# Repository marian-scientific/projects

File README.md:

# projects
project data, records &amp; publications

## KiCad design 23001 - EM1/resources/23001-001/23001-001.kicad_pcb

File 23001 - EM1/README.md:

# 23001 - EM1
### *Educational Manipulative 1*: Inequalities

## Associated Part Numbers:
- [23001-001](resources/23001-001/): USB-C charging LiPo power distribution test board

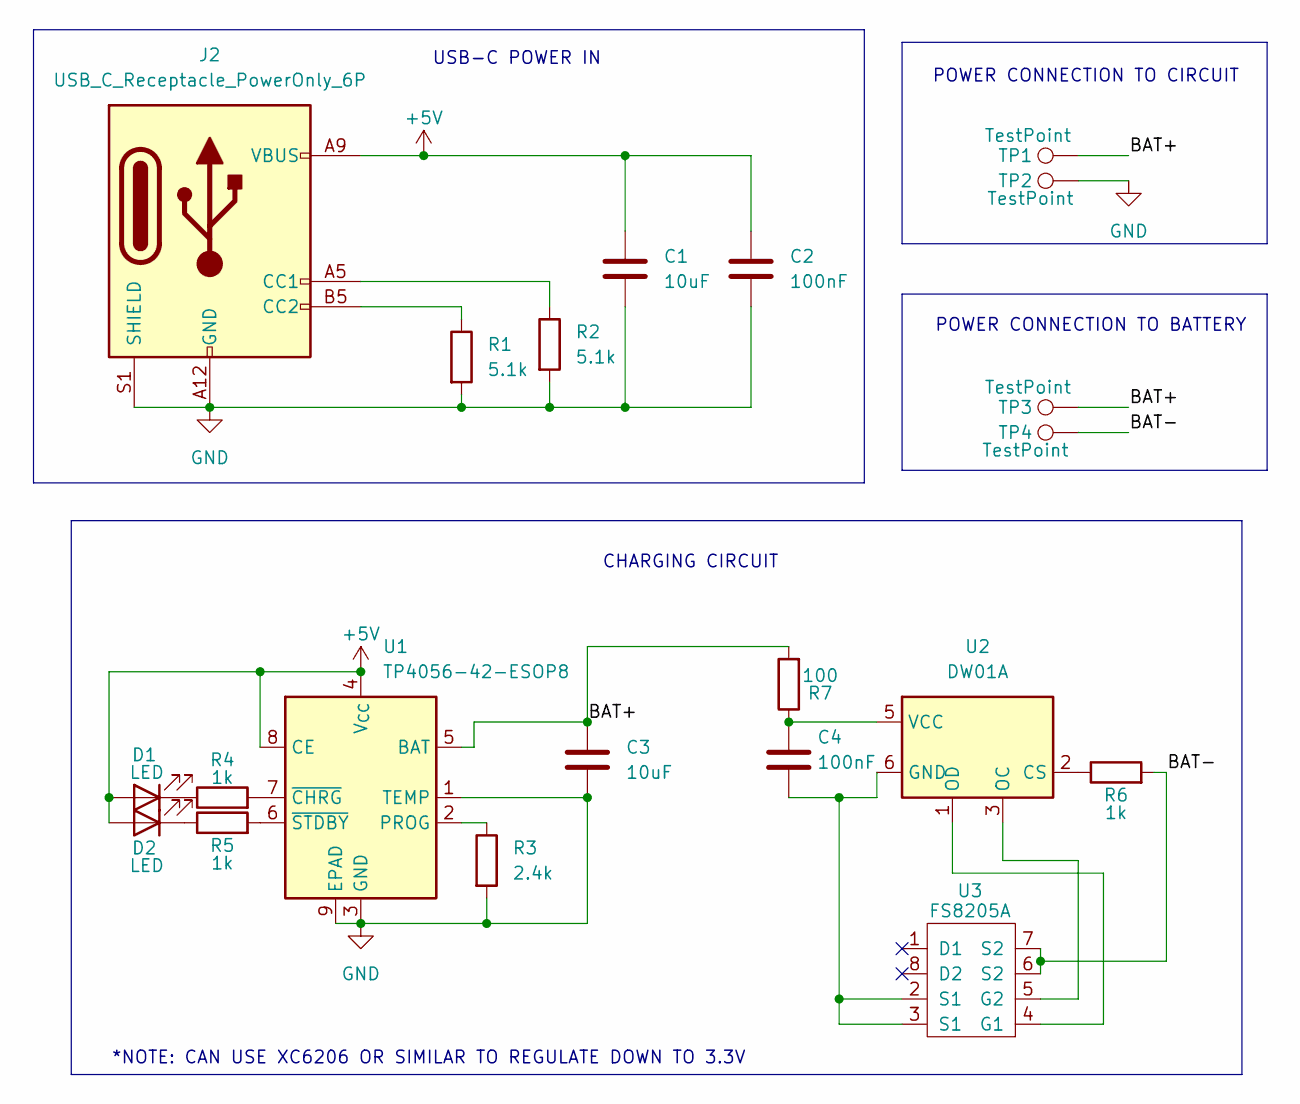
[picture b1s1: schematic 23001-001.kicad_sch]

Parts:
C1, C3: 10uF; C_1206_3216Metric
C2, C4: 100nF; C_1206_3216Metric
D1, D2: LED; LED_1206_3216Metric
J2: USB_C_Receptacle_PowerOnly_6P; USB_C_Receptacle_GCT_USB4125-xx-x_6P_TopMnt_Horizontal
R1, R2: 5.1k; R_1206_3216Metric
R3: 2.4k; R_1206_3216Metric
R4, R5, R6: 1k; R_1206_3216Metric
R7: 100; R_1206_3216Metric
TP1, TP2, TP3, TP4: TestPoint; TestPoint_THTPad_D2.5mm_Drill1.2mm
U1: TP4056-42-ESOP8; SOIC-8-1EP_3.9x4.9mm_P1.27mm_EP2.41x3.3mm_ThermalVias
U2: DW01A; SOT-23-6
U3: FS8205A; TSSOP-8_4.4x3mm_P0.65mm

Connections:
+5V: C1.1, C2.1, D1.2 (A), D2.2 (A), J2.A9 (VBUS), J2.B9 (VBUS), U1.4 (V_{CC}), U1.8 (CE)
/BAT+: C3.1, R7.2, TP1.1, TP3.1, U1.5 (BAT)
/BAT-: R6.2, TP4.1, U3.6 (S2), U3.7 (S2)
GND: C1.2, C2.2, C3.2, J2.A12 (GND), J2.B12 (GND), J2.S1 (SHIELD), R1.2, R2.2, R3.2, TP2.1, U1.1 (TEMP), U1.3 (GND), U1.9 (EPAD)
unnamed: D1.1 (K), R4.1
unnamed: D2.1 (K), R5.1
unnamed: J2.A5 (CC1), R2.1
unnamed: J2.B5 (CC2), R1.1
unnamed: R3.1, U1.2 (PROG)
unnamed: R4.2, U1.7 (~CHRG)
unnamed: R5.2, U1.6 (~STDBY)
unnamed: R6.1, U2.2 (CS)
unnamed: C4.2, U2.6 (GND), U3.2 (S1), U3.3 (S1)
unnamed: U2.3 (OC), U3.5 (G2)
unnamed: U2.1 (OD), U3.4 (G1)
unnamed: C4.1, R7.1, U2.5 (VCC)

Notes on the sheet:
CHARGING CIRCUIT
USB-C POWER IN
*NOTE: CAN USE XC6206 OR SIMILAR TO REGULATE DOWN TO 3.3V
POWER CONNECTION TO BATTERY
POWER CONNECTION TO CIRCUIT

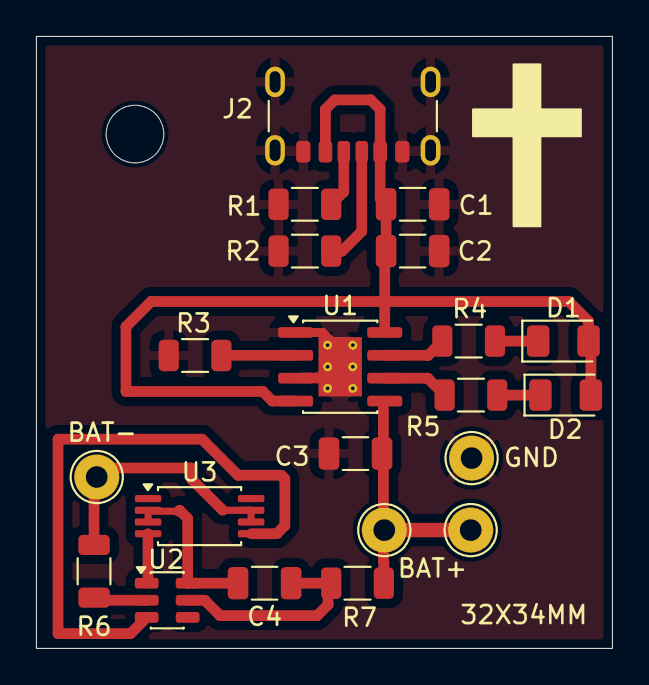
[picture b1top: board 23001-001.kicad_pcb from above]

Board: 2 copper layers, 32.0 x 34.0 mm, 21 parts (0 on the bottom side), 16 nets.

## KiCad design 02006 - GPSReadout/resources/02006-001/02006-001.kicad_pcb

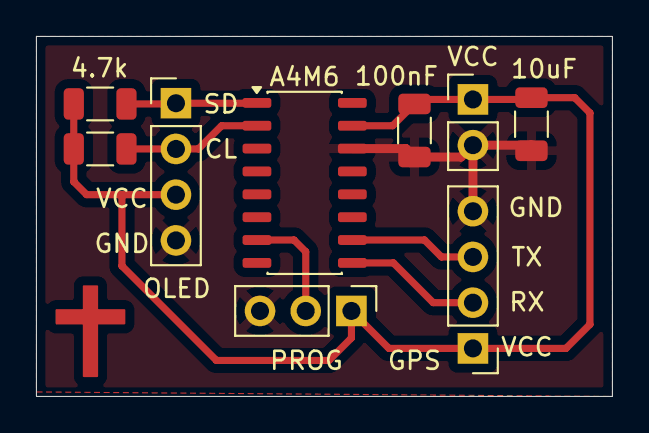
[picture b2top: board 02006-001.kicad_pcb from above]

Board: 2 copper layers, 32.0 x 20.0 mm, 9 parts (0 on the bottom side), 7 nets.

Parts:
4.7k: 4.7k; R_1206_3216Metric
10uF: 10uF; C_1206_3216Metric
100nF: 100nF; C_1206_3216Metric
A4M6: CH32V003AxMx; STC_SOP-16_3.9x9.9mm_P1.27mm
GPS: Conn_01x04_Pin; PinHeader_1x04_P2.54mm_Vertical
OLED: Conn_01x04_Pin; PinHeader_1x04_P2.54mm_Vertical
PROG: Conn_01x03_Pin; PinHeader_1x03_P2.54mm_Vertical
R1: 4.7k; R_1206_3216Metric
VCC: Conn_01x02_Pin; PinHeader_1x02_P2.54mm_Vertical

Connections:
/GPS_RX: A4M6.9 (PD5), GPS.2
/GPS_TX: A4M6.10 (PD6), GPS.3
/SCL: 4.7k.2, A4M6.2 (PC2), OLED.2
/SDA: A4M6.1 (PC1), OLED.1, R1.2
/SWDIO: A4M6.7 (PD1), PROG.2
GND: 10uF.2, 100nF.2, A4M6.14 (VSS), GPS.4, OLED.4, PROG.3, VCC.2
VCC: 4.7k.1, 10uF.1, 100nF.1, A4M6.15 (VDD), GPS.1, OLED.3, PROG.1, R1.1, VCC.1

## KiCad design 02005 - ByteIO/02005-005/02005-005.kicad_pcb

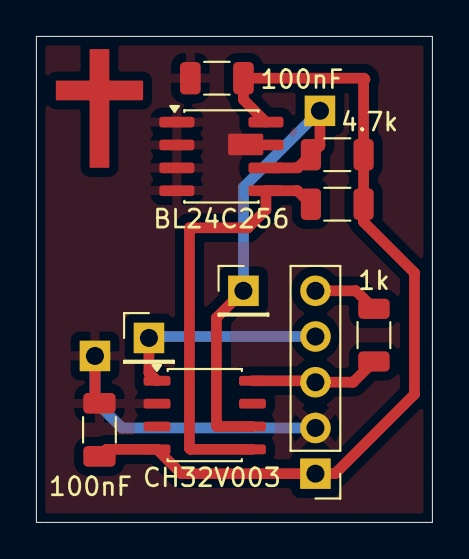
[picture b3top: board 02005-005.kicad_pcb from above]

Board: 2 copper layers, 22.0 x 27.0 mm, 8 parts (0 on the bottom side), 7 nets.

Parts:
1k: 1k; R_1206_3216Metric
4.7k: 4.7k; R_1206_3216Metric
100nF, 100nF#2: 100nF; C_1206_3216Metric
BL24C256: 24LC256; SOIC-8_3.9x4.9mm_P1.27mm
CH32V003: CH32V003JxMx; JEITA_SOIC-8_3.9x4.9mm_P1.27mm
J1: Conn_01x05_Pin; PinHeader_1x05_P2.54mm_Vertical
R2: 4.7k; R_1206_3216Metric

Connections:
/PROG_RX: CH32V003.1 (PD6/PA1), J1.4
/PROG_TX: 1k.2, J1.5
/SCL: 4.7k.1, BL24C256.6 (SCL), CH32V003.6 (PC2)
/SDA: BL24C256.5 (SDA), CH32V003.5 (PC1), R2.1
/SWDIO: 1k.1, CH32V003.8 (PD1/PD4/PD5), J1.3
GND: 100nF.2, 100nF#2.2, BL24C256.1 (A0), BL24C256.2 (A1), BL24C256.3 (A2), BL24C256.4 (GND), BL24C256.7 (WP), CH32V003.2 (VSS), J1.2
VCC: 4.7k.2, 100nF.1, 100nF#2.1, BL24C256.8 (VCC), CH32V003.4 (VDD), J1.1, R2.2

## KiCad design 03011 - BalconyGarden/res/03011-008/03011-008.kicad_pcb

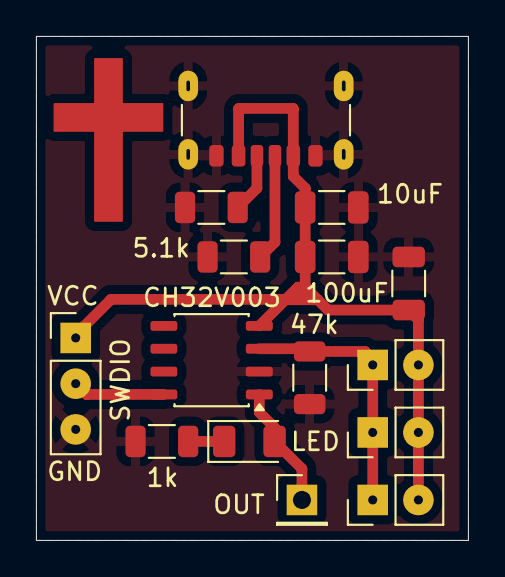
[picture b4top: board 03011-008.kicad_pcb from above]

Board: 2 copper layers, 24.0 x 28.0 mm, 15 parts (0 on the bottom side), 8 nets.

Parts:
1k: 1k; R_1206_3216Metric
5.1k: 5.1k; R_1206_3216Metric
10uF: 10uF; C_1206_3216Metric
47k: 47k; R_1206_3216Metric
100uF: 100nF; C_1206_3216Metric
C3: 100nF; C_1206_3216Metric
CH32V003: CH32V003JxMx; JEITA_SOIC-8_3.9x4.9mm_P1.27mm
J1: USB_C_Receptacle_PowerOnly_6P; USB_C_Receptacle_GCT_USB4125-xx-x_6P_TopMnt_Horizontal
J2, J3, J4: Conn_01x02_Pin; PinHeader_1x02_P2.54mm_Vertical
J5: Conn_01x03_Pin; PinHeader_1x03_P2.54mm_Vertical
LED: LED; LED_1206_3216Metric
OUT: Conn_01x01_Pin; PinHeader_1x01_P2.54mm_Vertical
R1: 5.1k; R_1206_3216Metric

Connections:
/FSR: 47k.1, CH32V003.3 (PA2), J2.1, J3.1, J4.1
/OUTPUT LED: CH32V003.1 (PD6/PA1), LED.2 (A), OUT.1
/SWDIO: CH32V003.8 (PD1/PD4/PD5), J5.2
GND: 1k.2, 5.1k.2, 10uF.2, 47k.2, 100uF.2, C3.2, CH32V003.2 (VSS), J1.A12 (GND), J1.B12 (GND), J1.S1 (SHIELD), J5.3, R1.2
unnamed: 1k.1, LED.1 (K)
unnamed: 5.1k.1, J1.A5 (CC1)
unnamed: J1.B5 (CC2), R1.1
VCC: 10uF.1, 100uF.1, C3.1, CH32V003.4 (VDD), J1.A9 (VBUS), J1.B9 (VBUS), J2.2, J3.2, J4.2, J5.1

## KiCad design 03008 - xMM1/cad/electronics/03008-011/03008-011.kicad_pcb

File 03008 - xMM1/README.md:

# 03008 - xMM1

First early childhood education mathematics manipulative to teach inequalities (greater than & less than). 

Uses an ATMEGA328P (for processing), 2x reed switches (to determine input device orientation), 4x large 7-segment displays (to display digits), and 4x RGB LEDs and a buzzer to give user feedback for correct/incorrect answers. The box is laser cut from both 1/4" plywood and acryllic (bottom, to show the internals).

Manipulative was a massive success in early testing with children aged 6-7.

## [Journal Entry Log (external link)](https://marian-scientific.org/journals/projects/03008.html)

## [CAD file](cad/03008.FCStd)

## [Final Code](code/008_full_project)

## Pictures:

Manipulative and power source:

Front and early input device (no sticker):

Back showing internals:

Input device front:

Input device rear:

2x 7-segment breakout board:

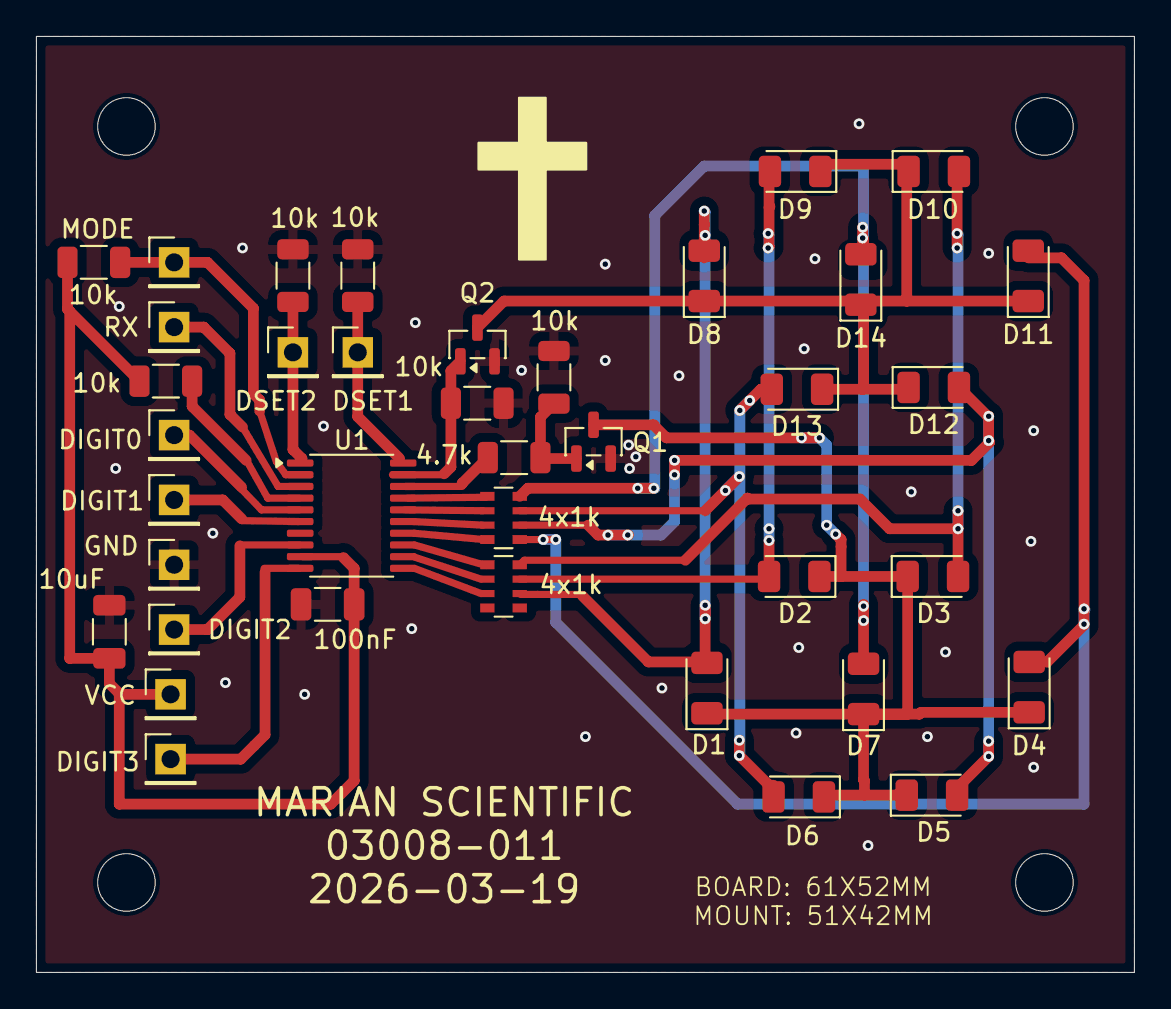
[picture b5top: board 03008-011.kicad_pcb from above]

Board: 2 copper layers, 61.0 x 52.0 mm, 38 parts (0 on the bottom side), 30 nets.

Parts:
4.7k, 10k, 10k#2, 10k#3, 10k#4, 10k#5, 10k#6: R; R_1206_3216Metric
4x1k, 4x1k#2: 4x1k; R_Array_Convex_4x0603
10uF: 10uF; C_1206_3216Metric
100nF: 100nF; C_1206_3216Metric
D1, D2, D3, D4, D5, D6, D7, D8, D9, D10, D11, D12, D13, D14: LED; LED_1206_3216Metric
DIGIT0, DIGIT1, DIGIT2, DIGIT3: Conn_01x01_Pin; PinHeader_1x01_P2.54mm_Vertical
DSET1, DSET2: Conn_01x01_Pin; PinHeader_1x01_P2.54mm_Vertical
GND: Conn_01x01_Pin; PinHeader_1x01_P2.54mm_Vertical
MODE: Conn_01x01_Pin; PinHeader_1x01_P2.54mm_Vertical
Q1, Q2: MMBT3904; SOT-23
RX: Conn_01x01_Pin; PinHeader_1x01_P2.54mm_Vertical
U1: CH32V003FxPx; TSSOP-20_4.4x6.5mm_P0.65mm
VCC: Conn_01x01_Pin; PinHeader_1x01_P2.54mm_Vertical

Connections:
GND: 10k.2, 10k#2.2, 10k#3.2, 10k#4.2, 10uF.2, 100nF.2, GND.1, Q1.2 (E), Q2.2 (E), U1.7 (VSS)
unnamed: 4x1k.6 (R3.2), D1.2 (A), D8.2 (A)
unnamed: D1.1 (K), D2.1 (K), D3.1 (K), D4.1 (K), D5.1 (K), D6.1 (K), D7.1 (K), Q1.3 (C)
unnamed: 4x1k.7 (R2.2), D2.2 (A), D9.2 (A)
unnamed: 4x1k.8 (R1.2), D3.2 (A), D10.2 (A)
unnamed: D8.1 (K), D9.1 (K), D10.1 (K), D11.1 (K), D12.1 (K), D13.1 (K), D14.1 (K), Q2.3 (C)
unnamed: 4x1k#2.5 (R4.2), D4.2 (A), D11.2 (A)
unnamed: 4x1k#2.6 (R3.2), D5.2 (A), D12.2 (A)
unnamed: 4x1k#2.7 (R2.2), D6.2 (A), D13.2 (A)
unnamed: 4x1k#2.8 (R1.2), D7.2 (A), D14.2 (A)
unnamed: DIGIT0.1, U1.5 (PA1)
unnamed: DIGIT1.1, U1.6 (PA2)
unnamed: DIGIT2.1, U1.8 (PD0)
unnamed: DIGIT3.1, U1.10 (PC0)
unnamed: 10k.1, DSET1.1, U1.20 (PD3)
unnamed: 10k#2.1, DSET2.1, U1.1 (PD4)
unnamed: 10k#5.2, MODE.1, U1.2 (PD5)
unnamed: 4.7k.2, 10k#3.1, Q1.1 (B)
unnamed: 10k#4.1, Q2.1 (B), U1.19 (PD2)
unnamed: 4x1k.1 (R1.1), U1.13 (PC3)
unnamed: 4x1k.2 (R2.1), U1.12 (PC2)
unnamed: 4x1k.3 (R3.1), U1.11 (PC1)
unnamed: 4x1k#2.1 (R1.1), U1.17 (PC7)
unnamed: 4x1k#2.2 (R2.1), U1.16 (PC6)
unnamed: 4x1k#2.3 (R3.1), U1.15 (PC5)
unnamed: 4x1k#2.4 (R4.1), U1.14 (PC4)
unnamed: RX.1, U1.3 (PD6)
unnamed: 4.7k.1, U1.18 (PD1)
unnamed: 10k#6.2, U1.4 (PD7)
VCC: 10k#5.1, 10k#6.1, 10uF.1, 100nF.1, U1.9 (VDD), VCC.1

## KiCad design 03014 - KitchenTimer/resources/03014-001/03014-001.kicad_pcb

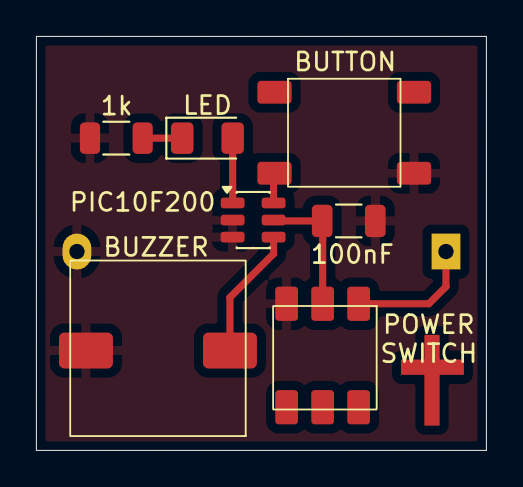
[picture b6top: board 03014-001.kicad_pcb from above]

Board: 2 copper layers, 25.0 x 23.0 mm, 8 parts (1 on the bottom side), 7 nets.

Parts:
1k: 1k; R_1206_3216Metric
BZ1: 9650\nACTIVE BUZZER; SMD_9650_ACTIVE_BUZZER
C1: 100nF; C_1206_3216Metric
CR2032 SOCKET: Battery_Cell; Battery_Panasonic_CR2032-HFN_Horizontal_CircularHoles
LED: LED; LED_1206_3216Metric
PIC10F200: PIC10F200-IOT; SOT-23-6
POWER SWITCH: SW_SPDT; SMD_5.8_5.8mm_PUSHBUTTON_LATCHING
SW2: SW_SPDT; SMD_6x6mm_PUSHBUTTON

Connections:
+3V0: CR2032 SOCKET.1 (+), POWER SWITCH.1 (A)
GND: 1k.2, BZ1.2 (-), C1.2, CR2032 SOCKET.2 (-), PIC10F200.2 (VSS), PIC10F200.3 (GP1), POWER SWITCH.3 (C), SW2.3 (C)
unnamed: BZ1.1 (+), PIC10F200.4 (GP2)
unnamed: LED.2 (A), PIC10F200.1 (GP0)
unnamed: 1k.1, LED.1 (K)
unnamed: C1.1, PIC10F200.5 (VDD), POWER SWITCH.2 (B)
unnamed: PIC10F200.6 (GP3), SW2.2 (B)

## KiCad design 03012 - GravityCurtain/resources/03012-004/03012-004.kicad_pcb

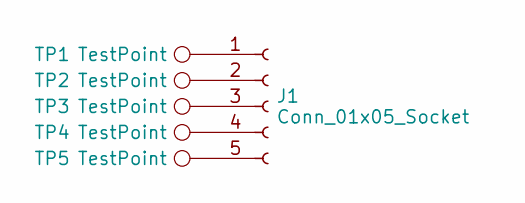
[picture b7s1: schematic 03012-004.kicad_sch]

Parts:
J1: Conn_01x05_Socket; PinSocket_1x05_P2.54mm_Vertical
TP1, TP2, TP3, TP4, TP5: TestPoint; TestPoint_THTPad_1.5x1.5mm_Drill0.7mm

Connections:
unnamed: J1.1, TP1.1
unnamed: J1.2, TP2.1
unnamed: J1.3, TP3.1
unnamed: J1.4, TP4.1
unnamed: J1.5, TP5.1

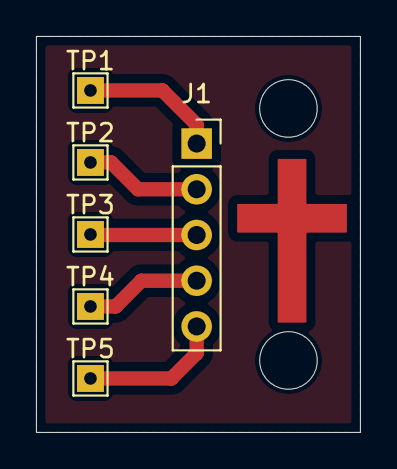
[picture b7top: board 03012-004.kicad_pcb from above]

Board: 2 copper layers, 18.0 x 22.0 mm, 6 parts (0 on the bottom side), 5 nets.

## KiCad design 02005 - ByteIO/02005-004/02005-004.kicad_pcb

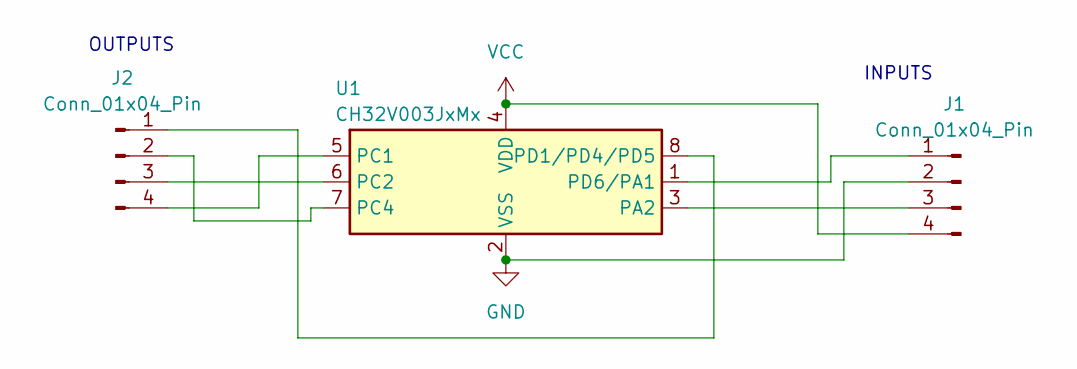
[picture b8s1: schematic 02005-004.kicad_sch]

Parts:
J1, J2: Conn_01x04_Pin; PinHeader_1x04_P2.54mm_Vertical
U1: CH32V003JxMx; JEITA_SOIC-8_3.9x4.9mm_P1.27mm

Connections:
GND: J1.2, U1.2 (VSS)
unnamed: J1.1, U1.1 (PD6/PA1)
unnamed: J1.3, U1.3 (PA2)
unnamed: J2.1, U1.8 (PD1/PD4/PD5)
unnamed: J2.2, U1.7 (PC4)
unnamed: J2.3, U1.6 (PC2)
unnamed: J2.4, U1.5 (PC1)
VCC: J1.4, U1.4 (VDD)

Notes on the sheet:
INPUTS
OUTPUTS

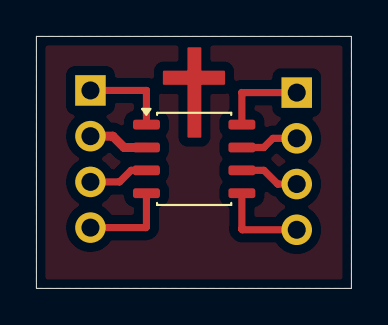
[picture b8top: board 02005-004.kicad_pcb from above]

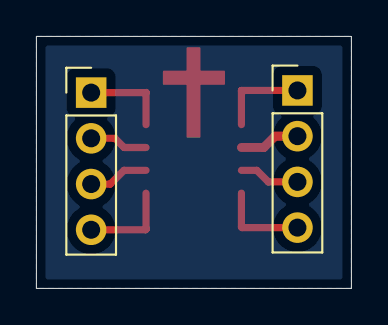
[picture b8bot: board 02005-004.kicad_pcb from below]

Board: 2 copper layers, 17.5 x 14.0 mm, 3 parts (2 on the bottom side), 8 nets.

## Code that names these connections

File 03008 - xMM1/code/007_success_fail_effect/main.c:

#include <stdlib.h>
#include <avr/io.h>
#include <util/delay.h>

// --- Buzzer Definitions ---
#define BUZZER_PIN PB1          // Timer1 OC1A output pin (Pin 9 on Port B)
#define PRESCALER 8             // Prescaler N = 8
#define PRESCALER_BITS (1 << CS11) // Set CS11 for N=8

// Ascending notes
#define NOTE_G4 318
#define NOTE_B4 252
#define NOTE_D5 212

// Dissonant notes
#define NOTE_A4   283
#define NOTE_BFLAT4 267

void start_tone(uint16_t top_value) {

    // Configure Timer1 for Fast PWM Mode (Mode 14)
    TCCR1A = (1 << WGM11);
    TCCR1B = (1 << WGM13) | (1 << WGM12);

    // Frequency
    ICR1 = top_value;

    // 50% duty cycle
    OCR1A = top_value / 2;

    // non-inverting output on OC1A
    TCCR1A |= (1 << COM1A1);

    // Set Prescaler to 8 and START the timer
    TCCR1B |= PRESCALER_BITS;
}

// Stops the tone by disabling the timer clock
void stop_tone() {
    TCCR1A &= ~((1 << COM1A1) | (1 << COM1A0));
    TCCR1B &= ~((1 << CS12) | (1 << CS11) | (1 << CS10)); // Clear prescaler bits
    PORTB &= ~(1 << BUZZER_PIN);
}

void sound(uint16_t NOTE) {
    uint16_t duration_ms = 150;
    start_tone(NOTE);
    _delay_ms(duration_ms);
    stop_tone();
}

void success() {

    PORTC &= ~(1 << PC5);
    PORTC |= (1 << PC3);

    uint16_t notes[] = {NOTE_G4, NOTE_B4, NOTE_D5};
    uint16_t duration_ms = 150;
    for (int i = 0; i < 3; i++) {
        start_tone(notes[i]);
        _delay_ms(duration_ms);
    }
    stop_tone();
    
}

void failure() {
    
    PORTC &= ~(1 << PC5);
    PORTC |= (1 << PC4);
    
    uint16_t notes[] = {NOTE_A4, NOTE_BFLAT4, NOTE_A4};
    uint16_t duration_ms = 150;
    for (int i = 0; i < 3; i++) {
        start_tone(notes[i]);
        _delay_ms(duration_ms);
    }
    stop_tone();
}


int main(void) {

    // INIT BUZZER
    DDRB |= (1 << BUZZER_PIN);
    
    // INIT REED SWITCHES
    DDRC &= ~(1 << PC0);
    DDRC &= ~(1 << PC1);
    PORTC |= (1 << PC0);  
    PORTC |= (1 << PC1); 

    // INIT LEDS
    DDRC |= (1 << PC3);
    DDRC |= (1 << PC4);
    DDRC |= (1 << PC5);
    PORTC &= ~(1 << PC3);
    PORTC &= ~(1 << PC4);
    PORTC &= ~(1 << PC5);
    
    while (1) {
  
	if (!(PINC & (1 << PC0))) {
	  	success();
		while (!(PINC & (1 << PC0)));
    		PORTC &= ~(1 << PC3);
	}
 	if (!(PINC & (1 << PC1))) {
		failure();
		while (!(PINC & (1 << PC1)));
    		PORTC &= ~(1 << PC4);
	}
    		PORTC |= (1 << PC5);
    }

    return 0;
}

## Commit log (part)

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2025-02-17 report draft, no code yet
2025-02-18 rename and res dir
2025-02-18 upload
2025-02-18 rename
2025-02-18 embed resources
2025-02-18 video
2025-02-18 test
2025-02-18 vid?
2025-02-18 reorder resources
2025-02-18 linebreak
2025-02-21 added code
2025-02-24 init reporting 03002
2025-02-24 upload pics
2025-02-24 rename and add pictures to status tracker
2025-02-24 update links and add final report template
2025-02-24 update links
2025-02-24 add RFP link
2025-02-24 add acronym
2025-02-25 feb 24
2025-02-27 feb 26
2025-02-28 feb 27
2025-03-01 chassis
2025-03-05 March 2 update
2025-03-05 mar 4
2025-03-06 mar 5
2025-03-11 march 7-9
2025-03-12 temp
2025-03-14 clean up
2025-03-14 begin report
2025-03-15 finish text
2025-03-15 add some pics
2025-03-15 final pics
2025-03-15 upload code
2025-03-19 create dir for 03005
2025-03-19 march 18 a
2025-03-19 format
2025-03-19 part dir added
2025-03-19 dont round hours
2025-03-20 march 19
2025-03-20 simpler
2025-03-22 mar 21
2025-03-23 mar 22
2025-03-24 mar 23
2025-03-24 typo
2025-03-25 3 24
2025-03-26 mar 25
2025-03-27 mar 26
2025-03-28 mar 27
2025-03-30 dirs
2025-03-30 template
2025-03-30 date
2025-03-31 init
2025-03-31 updated prototype date
2025-03-31 edits with mary
2025-03-31 updated some days with their videos
2025-03-31 spacing
2025-04-01 mar 31
2025-04-02 apr 1
2025-04-03 apr 2
2025-04-06 apr 4,5
2025-04-07 apr 6
2025-04-08 apr 7
2025-04-09 apr 8
2025-04-10 apr 9
2025-04-11 electrolysis
2025-04-11 apr 10
2025-04-12 apr 11
2025-04-12 pics
2025-04-12 apr 12
2025-04-13 03006 init
2025-04-16 Update PROGRESS_TRACKER.md
    April 14 & 15
2025-04-17 apr 16
2025-04-17 test results
2025-04-18 apr 17
2025-04-18 apr 18 start
2025-04-18 schematic link
2025-04-19 half of report
2025-04-19 draft done
2025-04-19 report submitted
2025-05-18 04001 init
2025-05-19 04002
2025-05-19 author
2025-05-20 02002
2025-05-20 parenthesis
2025-05-21 02003
2025-06-09 03007 start
2025-06-17 create directory
2025-06-17 resourcr directory
2025-06-26 Create bob
2025-06-26 preliminary report
2025-06-26 added schematic of buss
2025-06-28 added instructions
2025-06-29 added to results
2025-06-29 Updated the results and added a source
2025-07-02 rename directory, populate Readme
2025-07-03 finished 04003 master geometry & description and added sample geometry
2025-07-03 some grammar
2025-07-04 update description in readme
2025-07-09 Added the power rating
2025-07-09 Added an Abstract
2025-07-25 Added more References
2025-07-25 Added some more references
2025-07-26 Create PROGRESS_TRACKER.md
    progress tracker for the Alarm Machine project
2025-07-26 Added to the Progress Tracker for 02001
2025-07-26 added more to the Progress tracker
2025-07-26 added more to the progress tracker from document
2025-07-26 added more to the progress tracker document
2025-07-28 updated the progress tracker from the document
2025-07-28 Added paragraphs explaining the missing details of the progress tracker.
2025-07-28 Add files via upload
    adding image resourced for the motor prototype
2025-07-30 Added the objective and abstract
2025-07-30 Added parts list and experimenting with figures
2025-07-31 Added more to the design and procedure
2025-07-31 Added some edits
2025-07-31 Added the rest of the Body for the Motor Prototype Report
2025-07-31 Fixed the Table image
2025-09-20 Added more to the Report and added pictures
2025-09-20 fixed the jpegs not showing up
2025-09-21 Did more updates
2025-09-26 Added results section, results, and pics
2025-09-26 Fixed typos that didn't load in some pictures
2025-09-26 fixed trial 6 not loading in
2025-09-30 Create scratch dir
2025-09-30 spool winder batch 1 test
2025-10-02 handwritten AMF file for angies classroom
2025-11-02 rgb led working
2025-11-10 7seg working barely
2025-11-10 dirname typo
2025-11-14 4x 7seg
2025-11-16 03008 faceplate svg
2025-11-16 fingerspacer
2025-11-17 laser files
2025-11-20 03008-006 PCB
2025-11-20 added MM1 Minute Hand SVGs
2025-11-21 03008 reed switch holder & pcb support
2025-11-24 03008/4
2025-11-25 03008/005
2025-11-25 added amf parts of the cad files
2025-11-27 03008/_005
2025-11-29 03008/006
2025-11-30 03007 motor driver PCBs
2025-11-30 rename project 03007
2025-12-02 03008/007
2025-12-03 migrate CNC to 00001
2025-12-06 03008 / 008
2025-12-08 alligreater
2025-12-11 03008/008 rev
2025-12-12 03008 final code and cad files
2025-12-16 12001 init
2025-12-16 Fix README formatting and clarify reset instructions
    Updated instructions for resetting the board.
2025-12-17 12001/4/5
2025-12-18 12001/5/6
2025-12-20 working rp2040 avr programmer
2025-12-20 readme update
2025-12-21 12001-001
2025-12-21 final
2025-12-24 22001
2025-12-25 03010 - ruler svg
2025-12-26 03010-002
2025-12-26 updated 03010-002
2026-01-04 toner
2026-01-08 updated pcb design
2026-01-08 sticker
2026-01-10 code
2026-01-10 links
2026-01-13 Enhance README with usage and improvements
    Updated README with usage instructions and improvements details.
2026-01-19 03010 box assembly v0.1
2026-01-30 Create bob
    made bob
2026-01-30 02004 cleanup and assy
2026-01-30 toner transfer page & print gcode for ref
2026-02-01 updates and control input
2026-02-02 latest
2026-02-07 updated geometry for new hole locations
2026-02-07 toner transfer
2026-02-12 smol
2026-02-13 02004-004 fab files and 004T1
2026-02-14 02004-005
2026-02-15 silicone mat
2026-02-17 PCB mount
2026-02-19 rev board 03007-001
2026-02-21 03007-003
2026-02-24 03007-005/006
2026-02-24 smaller holes & masks
2026-02-25 02004-005 box
2026-02-26 updated housing
2026-02-27 03010-007
2026-02-28 box assy
2026-02-28 pcb rev
2026-03-02 03007-007 draft 2
2026-03-03 03007-007 pcb
2026-03-04 magnet sensor PCB designs
2026-03-05 02005-001
2026-03-05 add GND header
2026-03-06 02005-002
2026-03-07 02005-003
2026-03-08 42001
2026-03-08 00001-008
2026-03-08 03010-010
2026-03-09 03011-001
2026-03-09 03011-002
2026-03-10 03012-001
2026-03-11 03011 moisture detection boards
2026-03-12 03011-006
2026-03-13 03011-007
2026-03-14 00002-001
2026-03-15 03012-002
2026-03-16 03013-001
2026-03-17 03012-003
2026-03-18 02005-004
2026-03-18 02004 updated readme with pictures
2026-03-18 update main image size
2026-03-18 03012-004
2026-03-18 fix formatting
2026-03-19 03014-001
2026-03-20 03008-011
2026-03-21 03007-008
2026-03-22 03011-008
2026-03-23 02005-005
2026-03-23 02006-001
2026-03-23 3D primitives
2026-03-25 23001-001
2026-03-26 23001
2026-04-01 43001
2026-04-06 43001-003/4
2026-04-07 43003 and 4 and start documentation
2026-04-13 03008 documentation
2026-04-14 03012 draft mechanical components
2026-04-22 3d models
2026-04-23 00001-010
2026-04-28 various
2026-04-30 files
2026-05-14 cnc test
2026-05-17 00001-012 -013 -013A
2026-05-19 electrical panel plate
2026-05-19 sectional property computation, untested
2026-05-20 00001-014 and 015 spacers
2026-05-20 fixed error and added more properties
2026-05-23 slot insert parts 00001-016 and -017
2026-05-23 00001-017A
2026-05-24 00001-018
2026-05-26 00001-019
2026-05-27 fixed errors and validated EI calculations on Ibeam and rectangular bar
2026-06-10 00003 initial part geoms
